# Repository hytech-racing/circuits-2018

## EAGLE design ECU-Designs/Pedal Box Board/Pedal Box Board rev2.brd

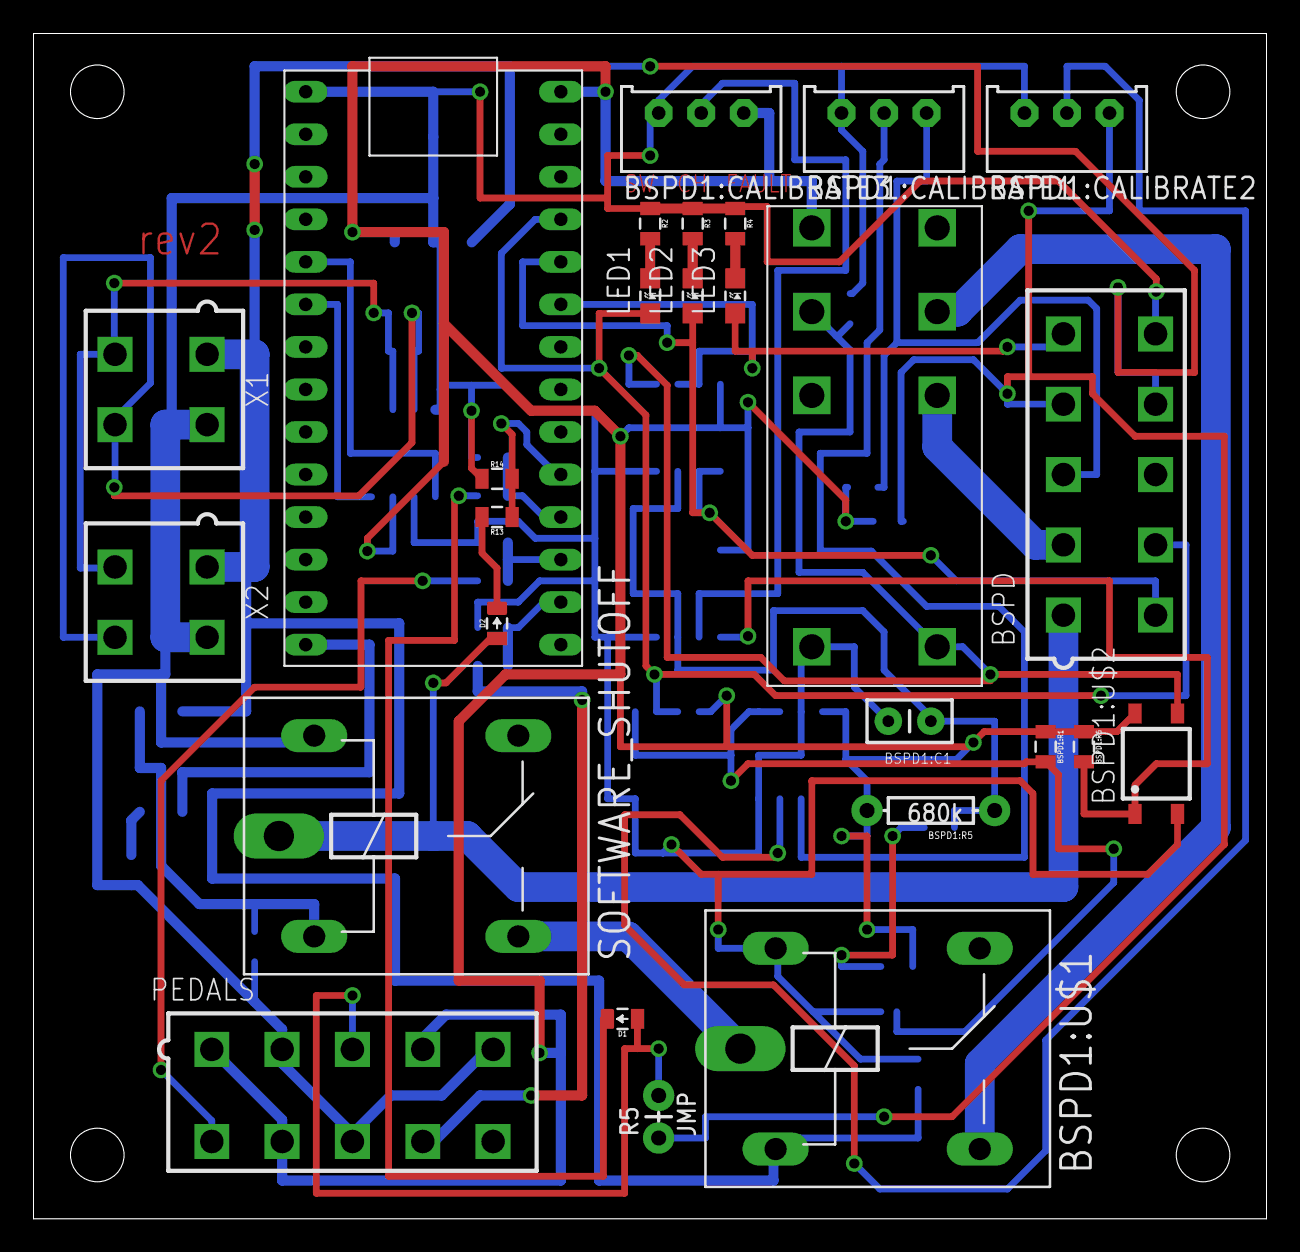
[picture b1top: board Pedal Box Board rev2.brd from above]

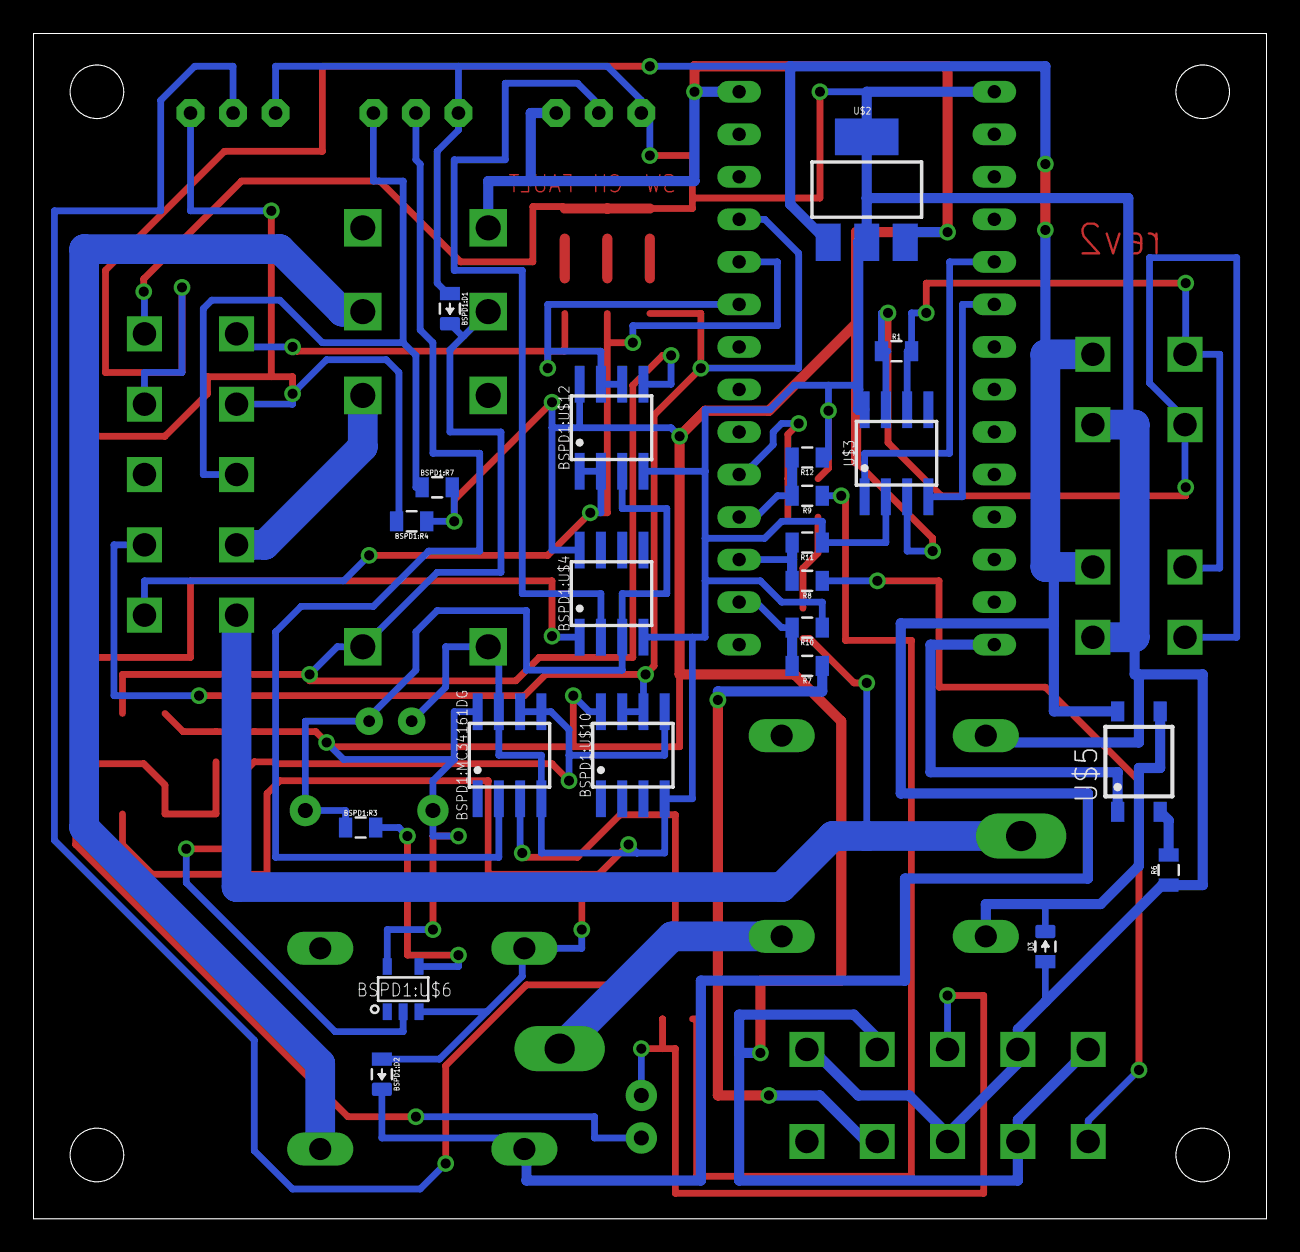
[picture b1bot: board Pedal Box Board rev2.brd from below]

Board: 2 copper layers, 73.6 x 70.8 mm, 49 parts (22 on the bottom side), 39 nets.

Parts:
BSPD: MINIFIT_5566-10
BSPD1:C1: .47u; CAP-PTH-SMALLEZ
BSPD1:CALIBRATE1, BSPD1:CALIBRATE2, BSPD1:CALIBRATE3: TRIMPOT_3296
BSPD1:D1, BSPD1:D2: DIODE0805; 0805_D
BSPD1:MC34161DG: SOIC-08
BSPD1:R1, BSPD1:R4, BSPD1:R7: 10k; 0805
BSPD1:R3: 330; 0805
BSPD1:R5: 680k; AXIAL-0.3EZ
BSPD1:R6: 680; 0805
BSPD1:U$1: G5LE; ZF112
BSPD1:U$2: CPC1002N; SOP04
BSPD1:U$3: JW2SN-DC5V; JW2SN
BSPD1:U$4: LM293DG4; SOIC-08
BSPD1:U$6: SN74LVC1G07; SOT-23-5
BSPD1:U$10, BSPD1:U$12: MCP6002SOIC; SOIC-08
D1, D2, D3: DIODE0805; 0805_D
LED1, LED2, LED3: LED-805
PEDALS: MINIFIT_5566-10
R1: 120; 0805
R2, R3, R4: 150; 0805
R5: JMP; AXIAL-0.1
R6: 100; 0805
R7, R8, R9: 10k; 0805
R10, R11, R12: 15k; 0805
R13: 43k; 0805
R14: 12k; 0805
SOFTWARE_SHUTOFF: G5LE; ZF112
U$1: TEENSY_3.2_SIMPLE
U$2: SOT223
U$3: MCP2551; SOIC-08
U$5: CPC1002N; SOP04
X1, X2: MINIFIT_5566-4

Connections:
+5V: BSPD1:CALIBRATE3.1, BSPD1:MC34161DG.8, BSPD1:R1.1, BSPD1:R4.1, BSPD1:R5.P$2, BSPD1:R6.1, BSPD1:R7.2, BSPD1:U$2.4, BSPD1:U$3.4, BSPD1:U$4.8, BSPD1:U$6.5, BSPD1:U$10.8, BSPD1:U$12.8, PEDALS.1, PEDALS.4, PEDALS.7, U$1.VIN, U$2.3, U$3.3
+12V: BSPD.9, BSPD1:D2.C, BSPD1:U$1.2, U$2.1, U$5.4, X1.1, X2.1
BSPD1:N$1: BSPD1:D1.C, BSPD1:U$2.3, BSPD1:U$3.3, BSPD1:U$3.COIL-, BSPD1:U$12.5
BSPD1:N$2: BSPD1:R3.2, BSPD1:U$6.4
BSPD1:N$5: BSPD1:CALIBRATE2.2, BSPD1:MC34161DG.3
BSPD1:N$6: BSPD1:CALIBRATE1.2, BSPD1:MC34161DG.2
BSPD1:N$7: BSPD1:CALIBRATE3.2, BSPD1:U$4.2
BSPD1:N$9: BSPD1:R6.2, BSPD1:U$2.1, BSPD1:U$4.1
BSPD1:N$10: BSPD1:MC34161DG.5, BSPD1:MC34161DG.6, BSPD1:R1.2, BSPD1:U$6.2, BSPD1:U$10.5
BSPD1:N$13: BSPD1:C1.1, BSPD1:R3.1, BSPD1:R5.P$1, BSPD1:U$4.3, BSPD1:U$12.3
BSPD1:SHUTDOWN_C: BSPD1:U$1.S, BSPD1:U$3.6
GND: BSPD.10, BSPD1:C1.2, BSPD1:CALIBRATE1.3, BSPD1:CALIBRATE2.3, BSPD1:CALIBRATE3.3, BSPD1:D1.A, BSPD1:D2.A, BSPD1:MC34161DG.4, BSPD1:MC34161DG.7, BSPD1:U$1.1, BSPD1:U$2.2, BSPD1:U$3.COIL+, BSPD1:U$4.4, BSPD1:U$6.3, BSPD1:U$10.4, BSPD1:U$12.4, D3.A, PEDALS.2, PEDALS.5, PEDALS.8, R2.1, R3.1, R4.1, R6.1, R10.1, R11.1, R12.1, R14.1, SOFTWARE_SHUTOFF.1, U$1.GND, U$2.2, U$2.4, U$3.2, U$3.8, X1.2, X2.2
unnamed: PEDALS.9, R7.1
unnamed: U$1.D4(CANRX), U$3.4
unnamed: R1.2, U$3.6, X1.3, X2.3
unnamed: R1.1, U$3.7, X1.4, X2.4
unnamed: U$1.D3(CANTX), U$3.1
unnamed: R8.2, R11.2, U$1.A1
unnamed: D1.C, R9.1
unnamed: PEDALS.6, R8.1
unnamed: R7.2, R10.2, U$1.A0
unnamed: R9.2, R12.2, U$1.A2
unnamed: D1.A, PEDALS.3, R5.P$2
unnamed: D3.C, SOFTWARE_SHUTOFF.2, U$5.3
unnamed: D2.C, R13.2
unnamed: LED1.C, R2.2
unnamed: LED2.C, R3.2
unnamed: LED3.C, R4.2
unnamed: R6.2, U$5.2
READ_CHARGE: BSPD.6, BSPD1:U$12.1, BSPD1:U$12.2, LED2.A, U$1.A8
READ_FAULT: BSPD.5, BSPD1:U$12.6, BSPD1:U$12.7, LED3.A, U$1.A7
READ_SWITCH: BSPD.7, BSPD1:U$10.6, BSPD1:U$10.7, LED1.A, U$1.A9
READ_UPSTREAM_SHUTDOWN: R13.1, R14.2, U$1.A3
SHUTDOWN_A: BSPD.1, D2.A, SOFTWARE_SHUTOFF.P
SHUTDOWN_B: BSPD1:U$1.P, SOFTWARE_SHUTOFF.S
SHUTDOWN_D: BSPD.2, BSPD1:U$3.7
SHUTDOWN_RELAY_CTRL: U$1.D12, U$5.1
SIGNAL_BRAKE: BSPD.4, BSPD1:CALIBRATE2.1, BSPD1:R4.2, R5.P$1
SIGNAL_CURRENT: BSPD.3, BSPD1:CALIBRATE1.1, BSPD1:R7.1

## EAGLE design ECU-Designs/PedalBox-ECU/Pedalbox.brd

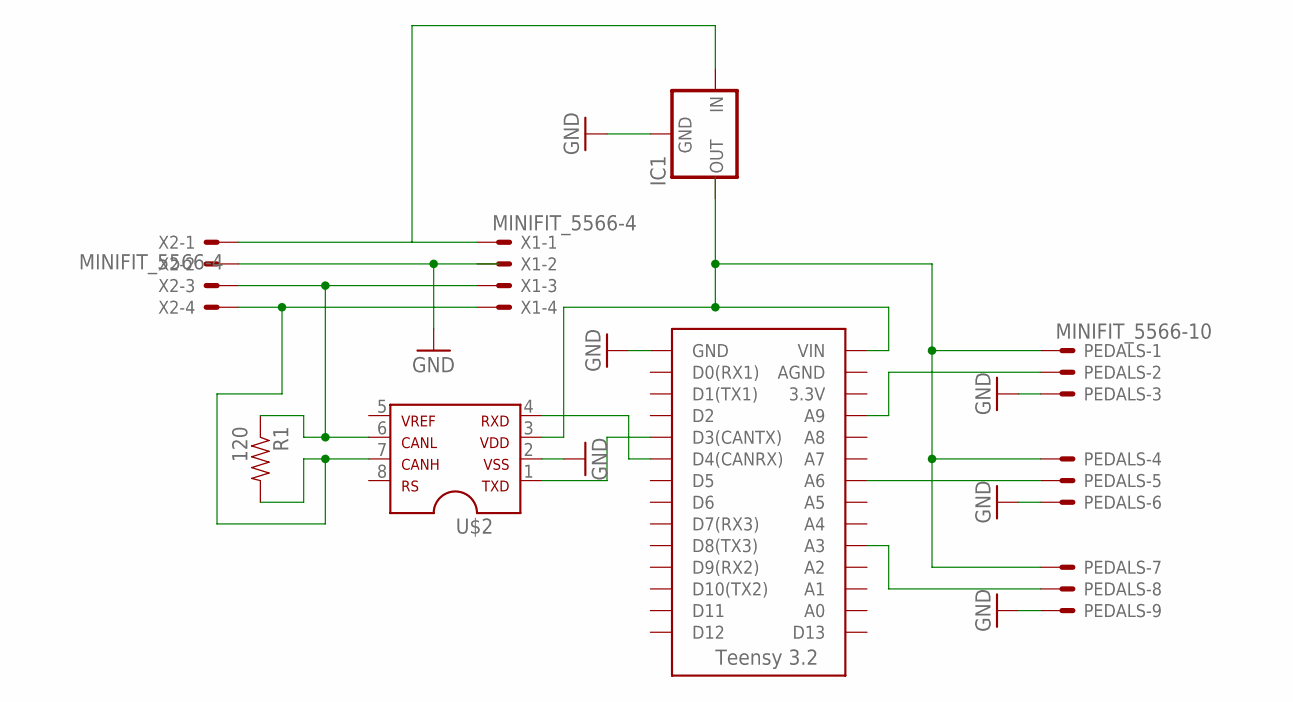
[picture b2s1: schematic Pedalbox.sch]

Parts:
IC1: 5V_REGULATOR_LM340-NLM340MPX-5.0/NOPB; SOT223
PEDALS: MINIFIT_5566-10
R1: 120; 0805
U$1: TEENSY_3.2_SIMPLE
U$2: MCP2551SOIC; SOIC08
X1, X2: MINIFIT_5566-4

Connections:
GND: IC1.2 (GND), IC1.4 (GND), PEDALS.3, PEDALS.6, PEDALS.9, U$1.GND, U$2.2, X2.2
unnamed: R1.2, U$2.7, X1.4, X2.4
unnamed: R1.1, U$2.6, X1.3, X2.3
unnamed: PEDALS.2, U$1.A9
unnamed: IC1.1 (IN), X1.1, X2.1
unnamed: PEDALS.5, U$1.A6
unnamed: PEDALS.8, U$1.A3
unnamed: PEDALS.1, PEDALS.4, PEDALS.7, U$1.VIN, U$2.3
unnamed: U$1.D4(CANRX), U$2.4
unnamed: U$1.D3(CANTX), U$2.1

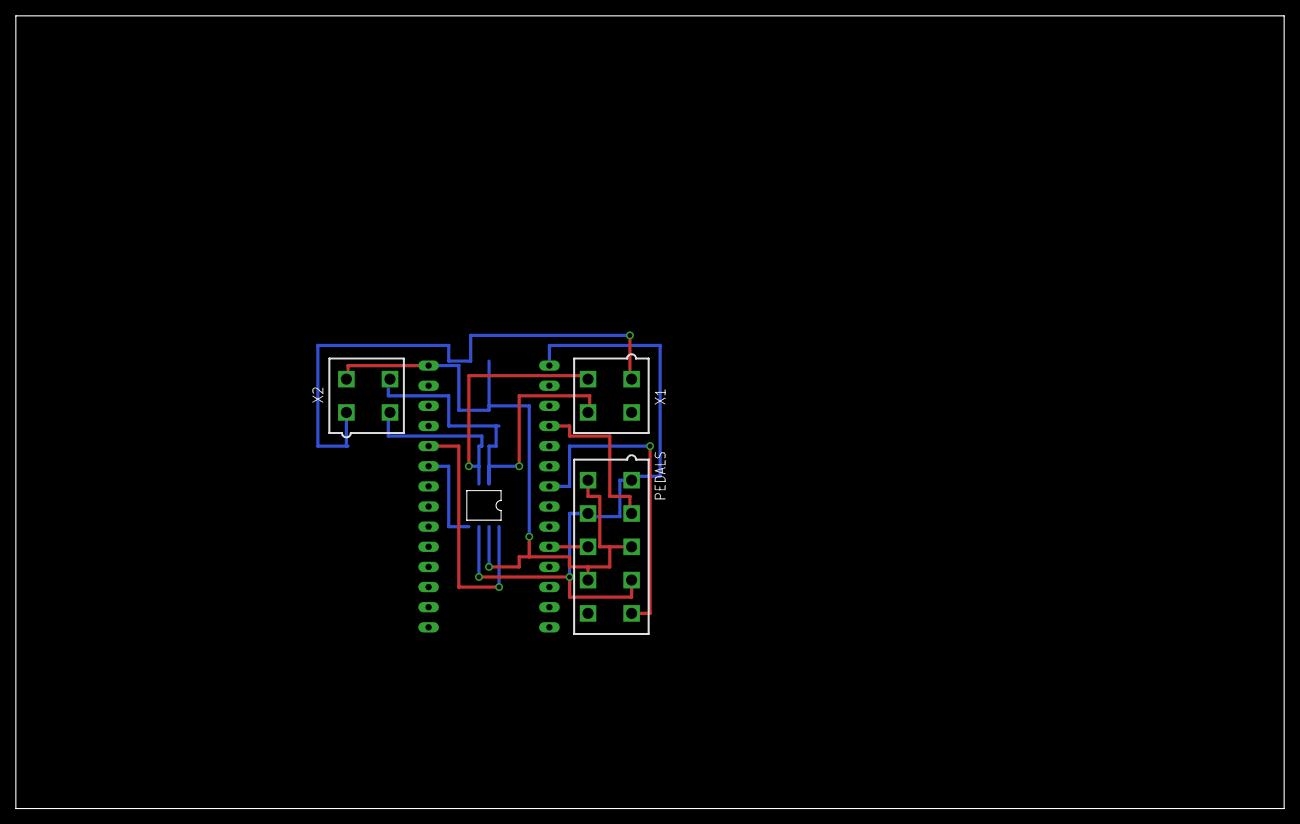
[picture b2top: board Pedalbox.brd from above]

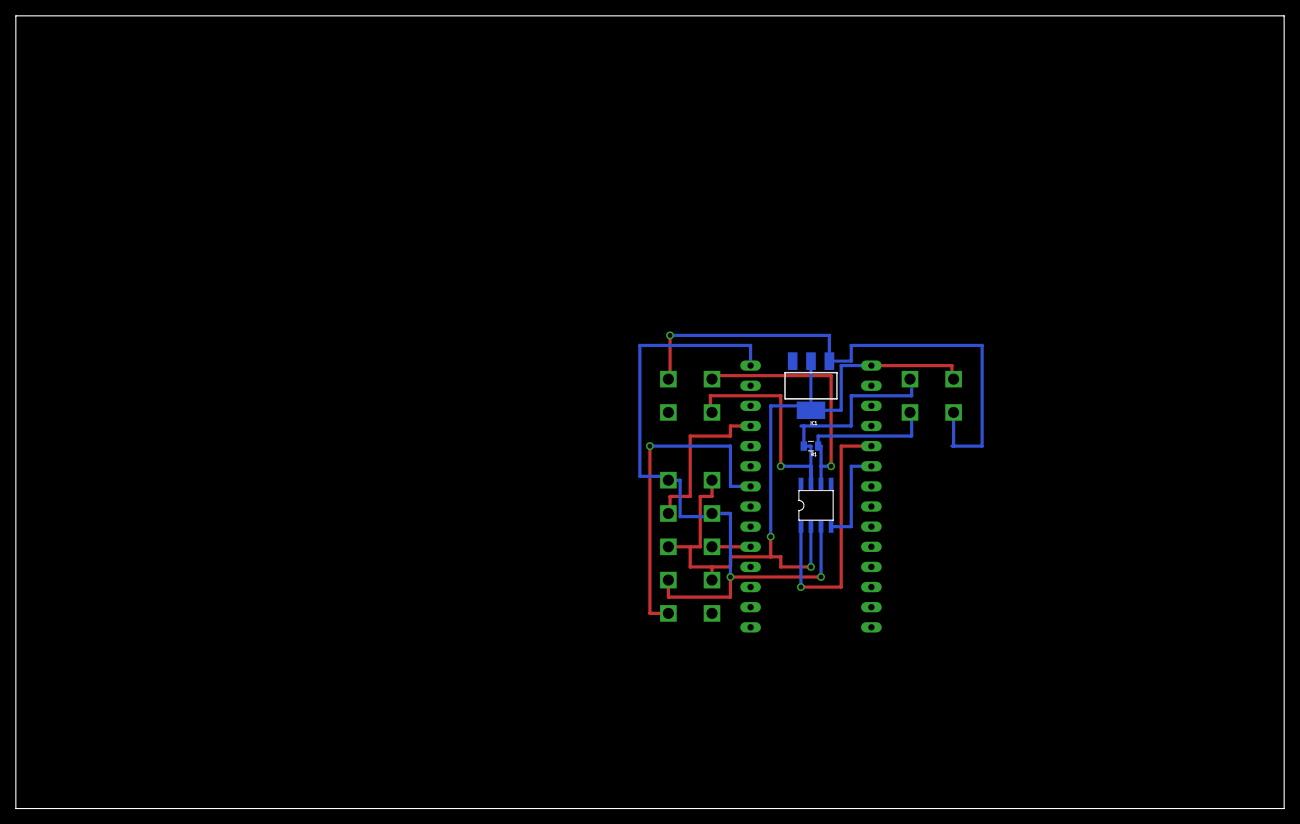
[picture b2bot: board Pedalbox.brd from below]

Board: 2 copper layers, 160.0 x 100.0 mm, 7 parts (3 on the bottom side), 10 nets.

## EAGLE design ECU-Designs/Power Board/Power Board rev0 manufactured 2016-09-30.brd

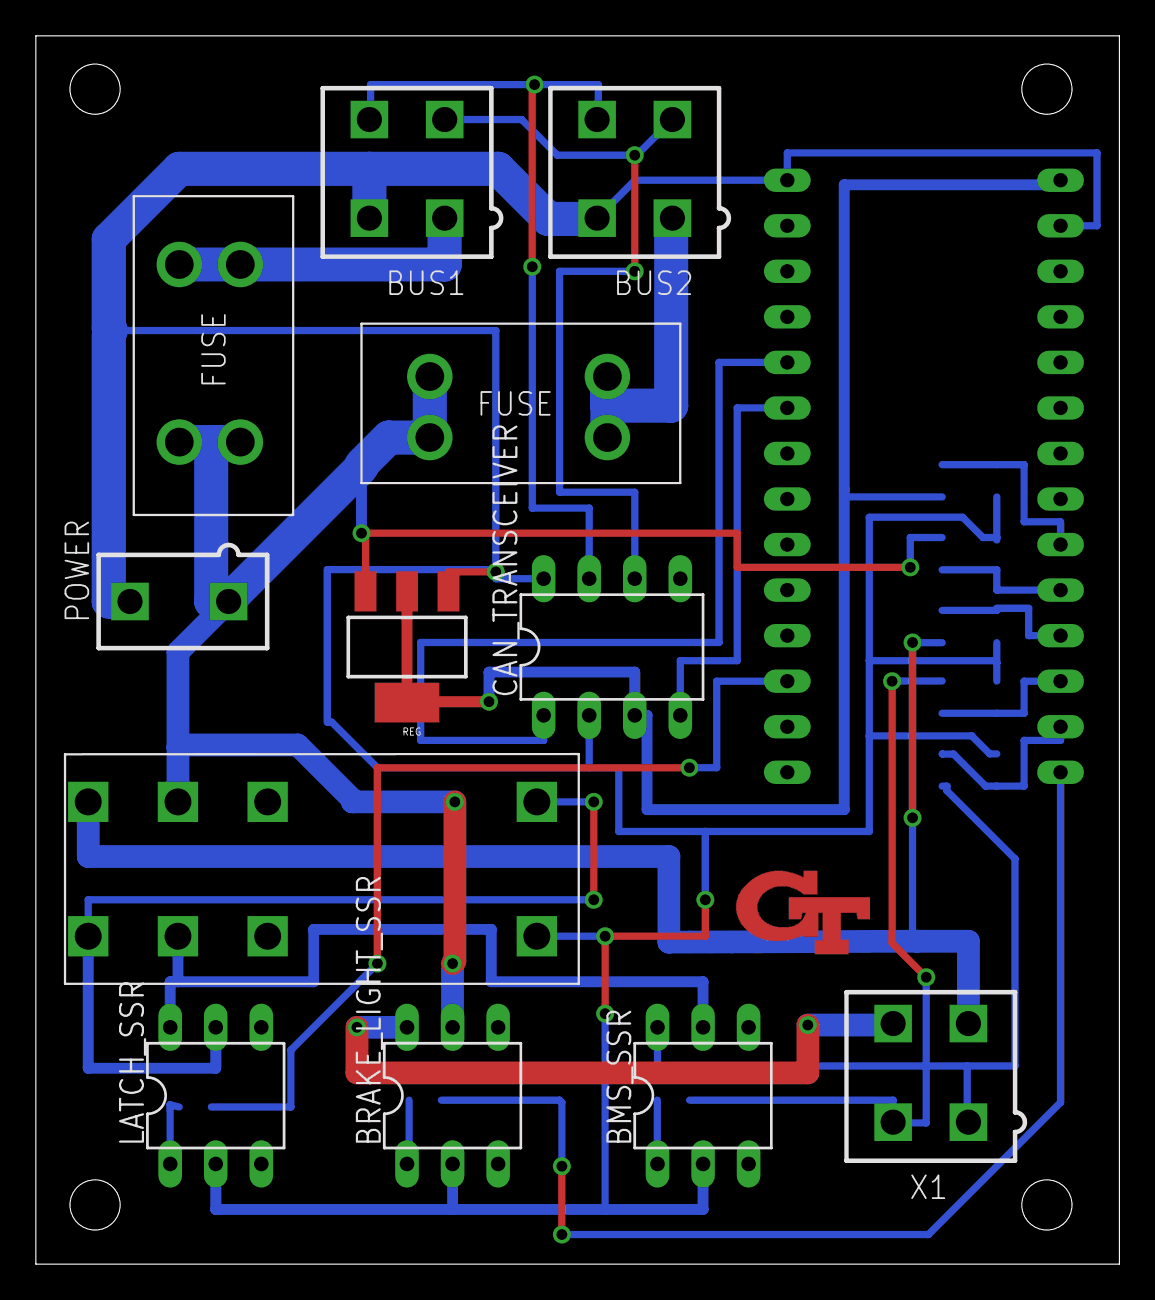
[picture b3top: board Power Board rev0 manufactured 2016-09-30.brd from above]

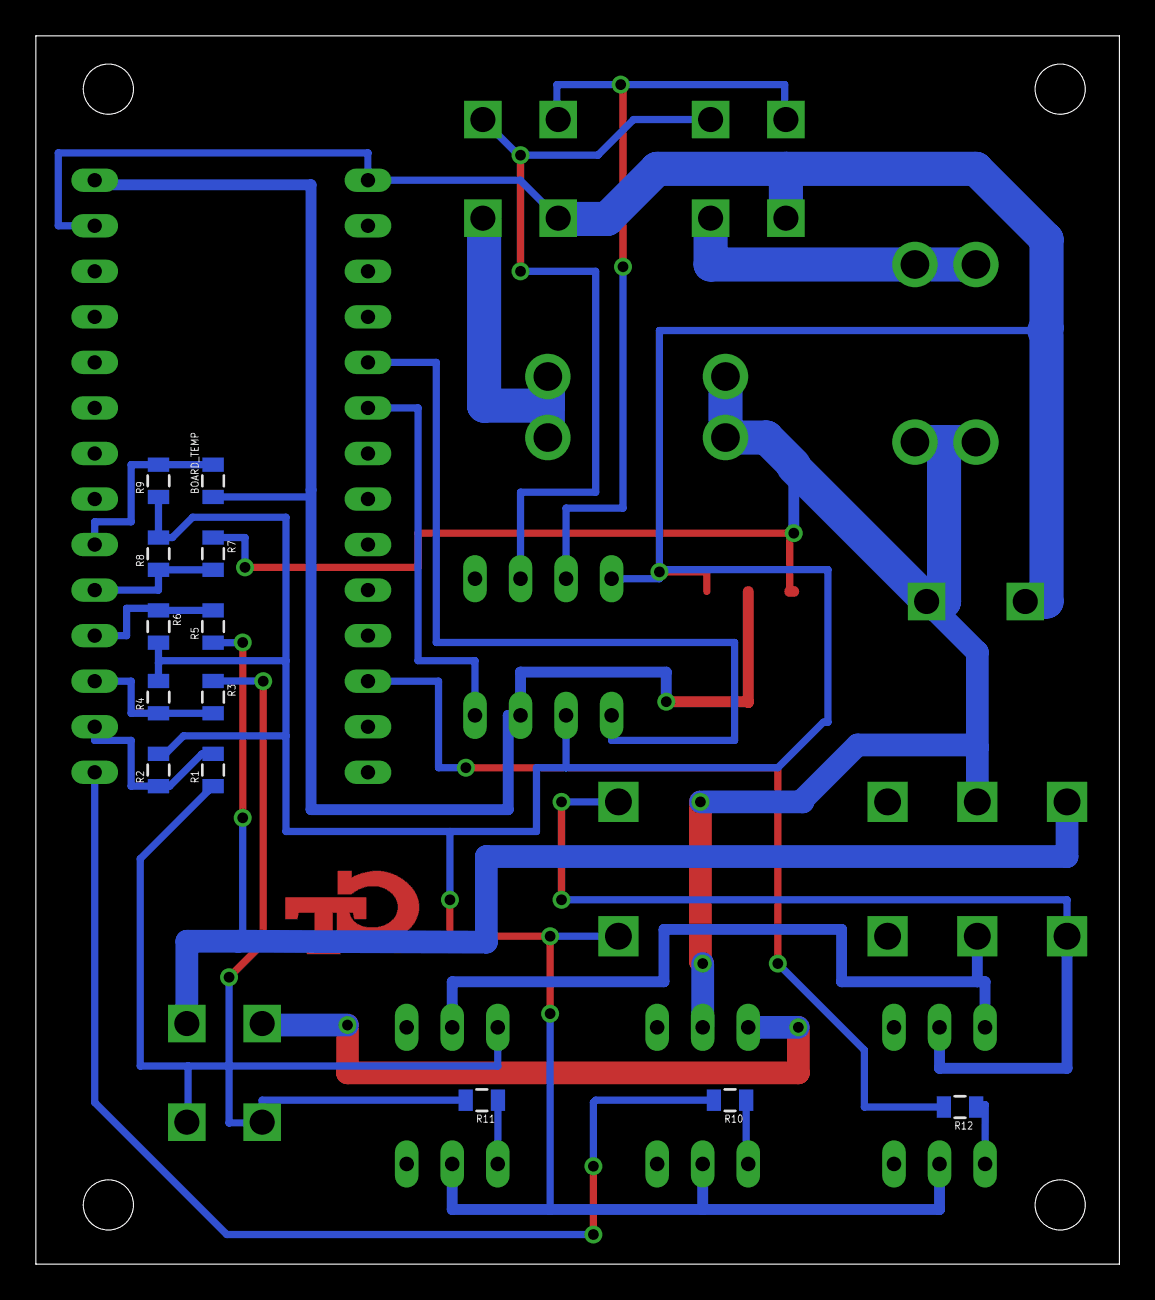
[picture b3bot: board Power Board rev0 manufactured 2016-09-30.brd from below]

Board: 2 copper layers, 60.4 x 68.5 mm, 26 parts (13 on the bottom side), 25 nets.

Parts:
BMS_SSR: SOLID_STATE_RELAY_VO14642AT; DIL06
BOARD_TEMP: THERMISTOR_NCP21; 0805
BRAKE_LIGHT_SSR: SOLID_STATE_RELAY_VO14642AT; DIL06
BUS1, BUS2: MINIFIT_5566-4
CAN_TRANSCEIVER: MCP2551; DIL08
FUSE_BUS_1, FUSE_BUS_2: 5A; FUSE_HOLDER
IMD_SHUTDOWN: DPDT_RELAY_PANASONIC_JW2SN-DC9V; DPDT_RELAY_PANASONIC_JW2SN
LATCH_SSR: SOLID_STATE_RELAY_VO14642AT; DIL06
POWER: MINIFIT_5566-2
R1, R2, R3, R4, R5, R6, R7, R8: 0805
R9, R10, R11, R12: 10k; 0805
REG: 5V; SOT223
U$3: TEENSY_3.2_SIMPLE
X1: MINIFIT_5566-4

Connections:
12VSUPPLY: BRAKE_LIGHT_SSR.5, FUSE_BUS_1.R1, FUSE_BUS_1.R2, FUSE_BUS_2.L1, FUSE_BUS_2.L2, IMD_SHUTDOWN.6, POWER.1, R7.1, REG.3
12VSUPPLY_READ: R7.2, R8.1, U$3.A3
BMS_OK: R3.1, R11.2, X1.2
BMS_OK_READ: R3.2, R4.1, U$3.A1
CANH: BUS1.4, BUS2.4, CAN_TRANSCEIVER.7
CANL: BUS1.3, BUS2.3, CAN_TRANSCEIVER.6
GND: BMS_SSR.2, BRAKE_LIGHT_SSR.2, BUS1.2, BUS2.2, CAN_TRANSCEIVER.2, CAN_TRANSCEIVER.8, IMD_SHUTDOWN.COIL+, LATCH_SSR.2, POWER.2, R2.2, R4.2, R6.2, R8.2, R9.1, REG.1, U$3.AGND, U$3.GND
unnamed: BOARD_TEMP.1, CAN_TRANSCEIVER.3, REG.2, REG.4, U$3.VIN
unnamed: CAN_TRANSCEIVER.4, U$3.D4(CANRX)
unnamed: CAN_TRANSCEIVER.1, U$3.D3(CANTX)
unnamed: BRAKE_LIGHT_SSR.6, X1.4
unnamed: R12.2, U$3.D10(TX2)
unnamed: IMD_SHUTDOWN.4, IMD_SHUTDOWN.COIL-, LATCH_SSR.5
unnamed: BRAKE_LIGHT_SSR.1, R10.1
unnamed: BMS_SSR.6, R1.1, X1.1
unnamed: BMS_SSR.1, R11.1
unnamed: BUS1.1, FUSE_BUS_1.L1, FUSE_BUS_1.L2
unnamed: BUS2.1, FUSE_BUS_2.R1, FUSE_BUS_2.R2
unnamed: LATCH_SSR.1, R12.1
unnamed: R10.2, U$3.D13
unnamed: BOARD_TEMP.2, R9.2, U$3.A4
OKHS: BMS_SSR.5, IMD_SHUTDOWN.3, LATCH_SSR.6
OKHS_READ: R1.2, R2.1, U$3.A0
SHUTDOWN_OUT: IMD_SHUTDOWN.5, R5.1, X1.3
SHUTDOWN_OUT_READ: R5.2, R6.1, U$3.A2

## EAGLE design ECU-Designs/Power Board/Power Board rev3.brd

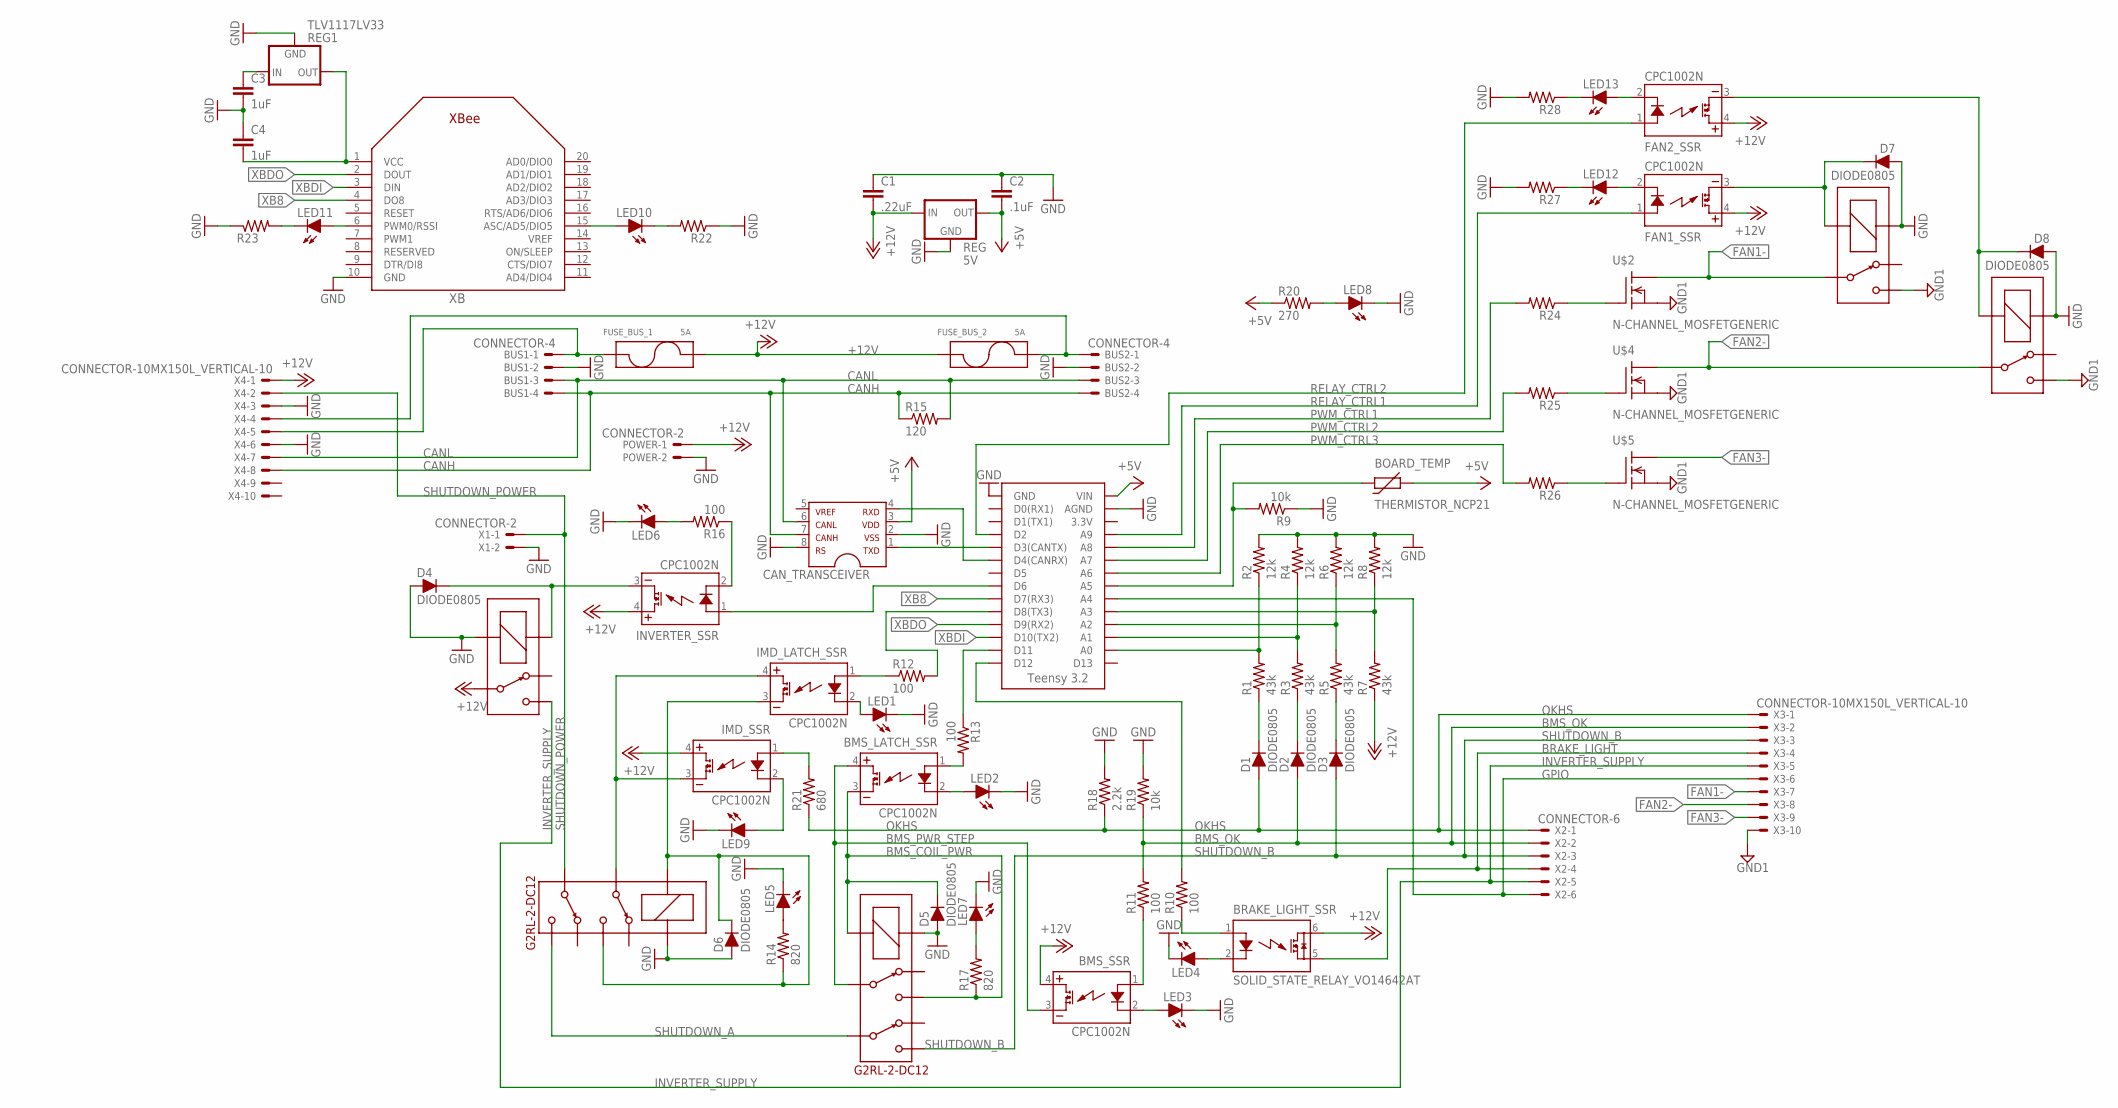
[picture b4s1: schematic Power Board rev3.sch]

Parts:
BMS_LATCH_SSR: CPC1002N; SOP04
BMS_SSR: CPC1002N; SOP04
BOARD_TEMP: THERMISTOR_NCP21; 0805
BRAKE_LIGHT_SSR: SOLID_STATE_RELAY_VO14642AT; DIL06
BUS1, BUS2: CONNECTOR-4; MINIFIT_5566-4
C1: .22uF; 0805
C2: .1uF; 0805
C3, C4: 1uF; 0805
CAN_TRANSCEIVER: MCP2551; SOIC-08
D1, D2, D3, D4, D5, D6, D7, D8: DIODE0805; 0805_D
FAN1_SSR, FAN2_SSR: CPC1002N; SOP04
FUSE_BUS_1, FUSE_BUS_2: 5A; MINI-BLADE_FUSE_HOLDER
IMD_LATCH_SSR: CPC1002N; SOP04
IMD_SHUTDOWN, IMD_SHUTDOWN1: G2RL-2-DC12; G2RL-2
IMD_SSR: CPC1002N; SOP04
INVERTER_SSR: CPC1002N; SOP04
LED1, LED2, LED3, LED4, LED5, LED6, LED7, LED8, LED9, LED10, LED11, LED12, LED13: LED-0805; LED-805
POWER: CONNECTOR-2; MINIFIT_5566-2
R1, R3, R5, R7: 43k; 0805
R2, R4, R6, R8: 12k; 0805
R9, R19: 10k; 0805
R10, R11, R12, R13, R16: 100; 0805
R14, R17: 820; 0805
R15: 120; 0805
R18: 2.2k; 0805
R20: 270; 0805
R21: 680; 0805
R22, R23, R24, R25, R26, R27, R28: RESISTOR0805-RES; 0805
REG: 5V; SOT223
REG1: TLV1117LV33; SOT223
U$1, U$6, U$7: G5LE; ZF112
U$2, U$4, U$5: N-CHANNEL_MOSFETGENERIC; TO-220-SINK
U$3: TEENSY_3.2_SIMPLE
X1: CONNECTOR-2; MINIFIT_5566-2
X2: CONNECTOR-6; MINIFIT_5566-6
X3, X4: CONNECTOR-10MX150L_VERTICAL-10; MX150L_VERTICAL-10
XB: XBEE

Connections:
12VSUPPLY_READ: R7.2, R8.1, U$3.A3
12V_F1: BUS1.1, FUSE_BUS_1.L1 (P1), FUSE_BUS_1.L2 (P1), X4.5
12V_F2: BUS2.1, FUSE_BUS_2.R1 (P2), FUSE_BUS_2.R2 (P2), X4.4
+5V: BOARD_TEMP.1, C2.2, CAN_TRANSCEIVER.3, R20.1, REG.3 (OUT), U$3.VIN
+12V: BMS_SSR.4 (DC+), BRAKE_LIGHT_SSR.6 (IO1), C1.2, FAN1_SSR.4 (DC+), FAN2_SSR.4 (DC+), FUSE_BUS_1.R1 (P2), FUSE_BUS_1.R2 (P2), FUSE_BUS_2.L1 (P1), FUSE_BUS_2.L2 (P1), IMD_SSR.4 (DC+), INVERTER_SSR.4 (DC+), POWER.1, R7.1, REG.1 (IN), U$1.P, X4.1
BMS_COIL_PWR: BMS_LATCH_SSR.3 (DC-), D5.C, IMD_SHUTDOWN1.4, IMD_SHUTDOWN1.COIL-, R17.1
BMS_OK: D2.A, R11.2, R19.1, X2.2, X3.2
BMS_OK_READ: R3.2, R4.1, U$3.A1
BMS_PWR_STEP: BMS_LATCH_SSR.4 (DC+), BMS_SSR.3 (DC-), IMD_SHUTDOWN1.3
BRAKE_LIGHT: BRAKE_LIGHT_SSR.5 (IO2), X2.4, X3.4
CANH: BUS1.4, BUS2.4, CAN_TRANSCEIVER.7, R15.1, X4.8
CANL: BUS1.3, BUS2.3, CAN_TRANSCEIVER.6, R15.2, X4.7
FAN1-: U$2.2 (D), U$6.P, X3.7
FAN2-: U$4.2 (D), U$7.P, X3.8
FAN3-: U$5.2 (D), X3.9
GND: BUS1.2, BUS2.2, C1.1, C2.1, C3.2, C4.1, CAN_TRANSCEIVER.2, CAN_TRANSCEIVER.8, D4.A, D5.A, D6.A, D7.A, D8.A, IMD_SHUTDOWN.COIL+, IMD_SHUTDOWN1.COIL+, LED1.C, LED2.C, LED3.C, LED4.C, LED5.C, LED6.C, LED7.C, LED8.C, LED9.C, POWER.2, R2.2, R4.2, R6.2, R8.2, R9.1, R18.2, R19.2, R22.1, R23.1, R27.2, R28.2, REG.2 (GND), REG.4 (GND), REG1.1 (GND), U$1.2 (COIL-), U$3.AGND, U$3.GND, U$6.1 (COIL+), U$7.1 (COIL+), X1.2, X4.3, X4.6, XB.10 (GND)
GND1: U$2.3 (S), U$4.3 (S), U$5.3 (S), U$6.S, U$7.S, X3.10
GPIO: U$3.A4, X2.6, X3.6
INVERTER_SUPPLY: U$1.S, X2.5, X3.5
unnamed: IMD_LATCH_SSR.2 (CONTROL-), LED1.A
unnamed: CAN_TRANSCEIVER.4, U$3.D4(CANRX)
unnamed: CAN_TRANSCEIVER.1, U$3.D3(CANTX)
unnamed: D7.C, FAN1_SSR.3 (DC-), U$6.2 (COIL-)
unnamed: IMD_LATCH_SSR.1 (CONTROL+), R12.1
unnamed: D6.C, IMD_LATCH_SSR.3 (DC-), IMD_SHUTDOWN.4, IMD_SHUTDOWN.COIL-, R14.1
unnamed: BRAKE_LIGHT_SSR.2 (LED-), LED4.A
unnamed: R12.2, U$3.D8(TX3)
unnamed: BMS_SSR.2 (CONTROL-), LED3.A
unnamed: LED10.A, XB.15 (ASC/AD5/DIO5)
unnamed: LED10.C, R22.2
unnamed: BMS_LATCH_SSR.1 (CONTROL+), R13.2
unnamed: R10.2, U$3.D12
unnamed: R13.1, U$3.D11
unnamed: BOARD_TEMP.2, R9.2, U$3.A5
unnamed: BMS_LATCH_SSR.2 (CONTROL-), LED2.A
unnamed: BRAKE_LIGHT_SSR.1 (LED+), R10.1
unnamed: BMS_SSR.1 (CONTROL+), R11.1
unnamed: LED5.A, R14.2
unnamed: D8.C, FAN2_SSR.3 (DC-), U$7.2 (COIL-)
unnamed: INVERTER_SSR.1 (CONTROL+), U$3.D6
unnamed: D1.C, R1.1
unnamed: D2.C, R3.1
unnamed: D3.C, R5.1
unnamed: LED11.A, XB.6 (PWM0/RSSI)
unnamed: D4.C, INVERTER_SSR.3 (DC-), U$1.1 (COIL+)
unnamed: INVERTER_SSR.2 (CONTROL-), R16.1
unnamed: LED6.A, R16.2
unnamed: LED8.A, R20.2
unnamed: IMD_LATCH_SSR.4 (DC+), IMD_SHUTDOWN.3, IMD_SSR.3 (DC-)
unnamed: IMD_SSR.1 (CONTROL+), R21.2
unnamed: LED7.A, R17.2
unnamed: LED11.C, R23.2
unnamed: IMD_SSR.2 (CONTROL-), LED9.A
unnamed: C3.1, REG1.3 (IN)
unnamed: LED13.C, R28.1
unnamed: LED12.C, R27.1
unnamed: FAN1_SSR.2 (CONTROL-), LED12.A
unnamed: R24.1, U$2.1 (G)
unnamed: R25.1, U$4.1 (G)
unnamed: R26.1, U$5.1 (G)
unnamed: FAN2_SSR.2 (CONTROL-), LED13.A
OKHS: D1.A, R18.1, R21.1, X2.1, X3.1
OKHS_READ: R1.2, R2.1, U$3.A0
PWM_CTRL1: R24.2, U$3.A8
PWM_CTRL2: R25.2, U$3.A7
PWM_CTRL3: R26.2, U$3.A6
RELAY_CTRL1: FAN1_SSR.1 (CONTROL+), U$3.A9
RELAY_CTRL2: FAN2_SSR.1 (CONTROL+), U$3.D2
SHUTDOWN_A: IMD_SHUTDOWN.5, IMD_SHUTDOWN1.6
SHUTDOWN_B: D3.A, IMD_SHUTDOWN1.5, X2.3, X3.3
SHUTDOWN_OUT_READ: R5.2, R6.1, U$3.A2
SHUTDOWN_POWER: IMD_SHUTDOWN.6, X1.1, X4.2
VCC: C4.2, REG1.2 (OUT), REG1.4 (OUT), XB.1 (VCC)
XB8: U$3.D7(RX3), XB.4 (DO8)
XBDI: U$3.D10(TX2), XB.3 (DIN)
XBDO: U$3.D9(RX2), XB.2 (DOUT)

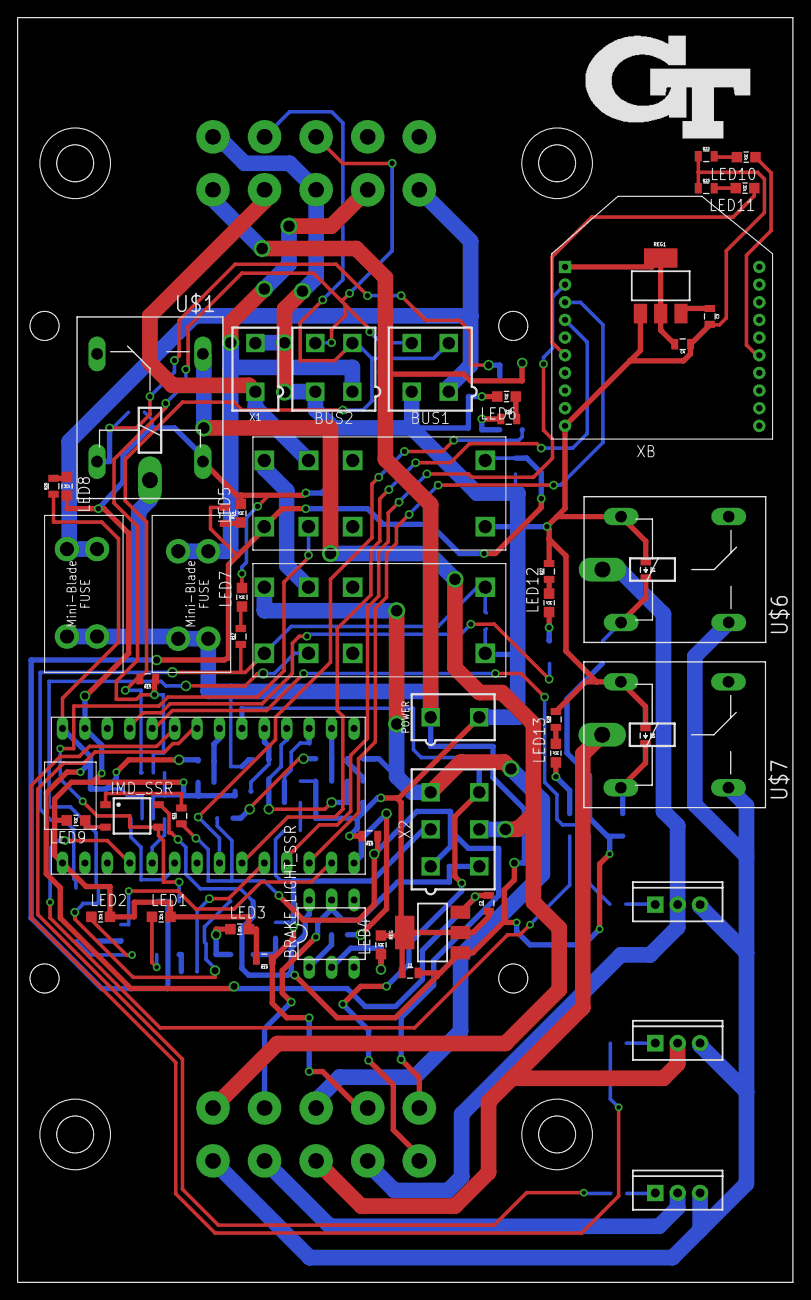
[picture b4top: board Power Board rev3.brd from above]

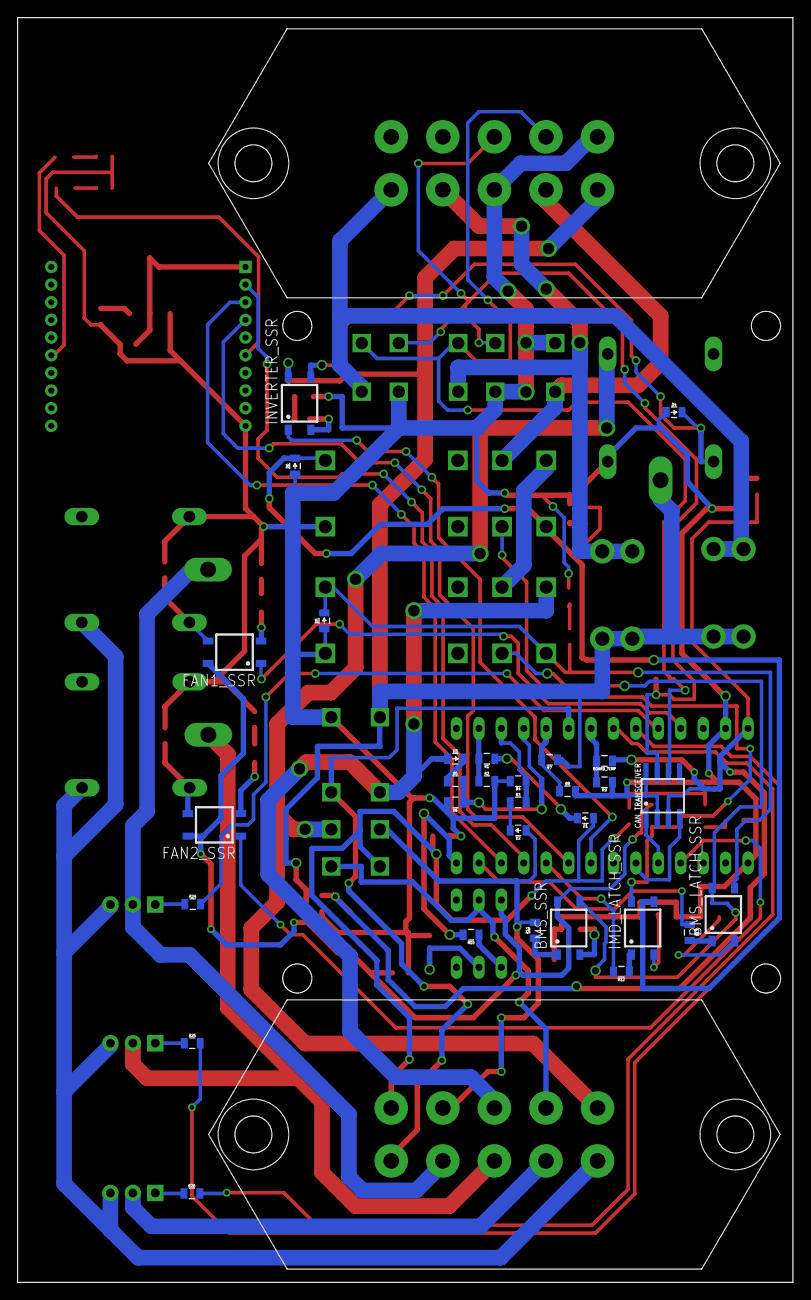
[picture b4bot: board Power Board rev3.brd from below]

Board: 2 copper layers, 87.8 x 143.2 mm, 84 parts (32 on the bottom side), 76 nets.
